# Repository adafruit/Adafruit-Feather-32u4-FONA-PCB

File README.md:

## Adafruit Feather 32u4 FONA PCB
<a href="http://www.adafruit.com/products/3027"><br/>
Click here to purchase one from the Adafruit shop</a>

This is the Adafruit Feather 32u4 FONA - our take on an 'all-in-one' Arduino-compatible + audio/sms/data capable cellular with built in USB and battery charging. Its an Adafruit Feather 32u4 with a FONA800 module, ready to rock! We have other boards and accessories in the Feather family, check'em out here.

At the Feather 32u4's heart is at ATmega32u4 clocked at 8 MHz and at 3.3V logic, a chip setup we've had tons of experience with as it's the same as the Flora. This chip has 32K of flash and 2K of RAM, with built in USB so not only does it have a USB-to-Serial program & debug capability built in with no need for an FTDI-like chip, it can also act like a mouse, keyboard, USB MIDI device, etc.

Since you'll be taking this on the road, we added a connector for any of our 3.7V Lithium polymer batteries and built in battery charging. A 500mAh+ Lipoly battery is required for use, it keeps the cellular module happy during the high current spikes. Plug the Feather into microUSB to charge at 500mA.

PCB files for Adafruit Feather 32u4 FONA. The format is EagleCAD schematic and board layout
- https://www.adafruit.com/product/3027

### License

Adafruit invests time and resources providing this open source design, please support Adafruit and open-source hardware by purchasing products from [Adafruit](https://www.adafruit.com)!

All text above must be included in any redistribution

Designed by Limor Fried/Ladyada for Adafruit Industries.
Creative Commons Attribution/Share-Alike, all text above must be included in any redistribution. 
See license.txt for additional information.

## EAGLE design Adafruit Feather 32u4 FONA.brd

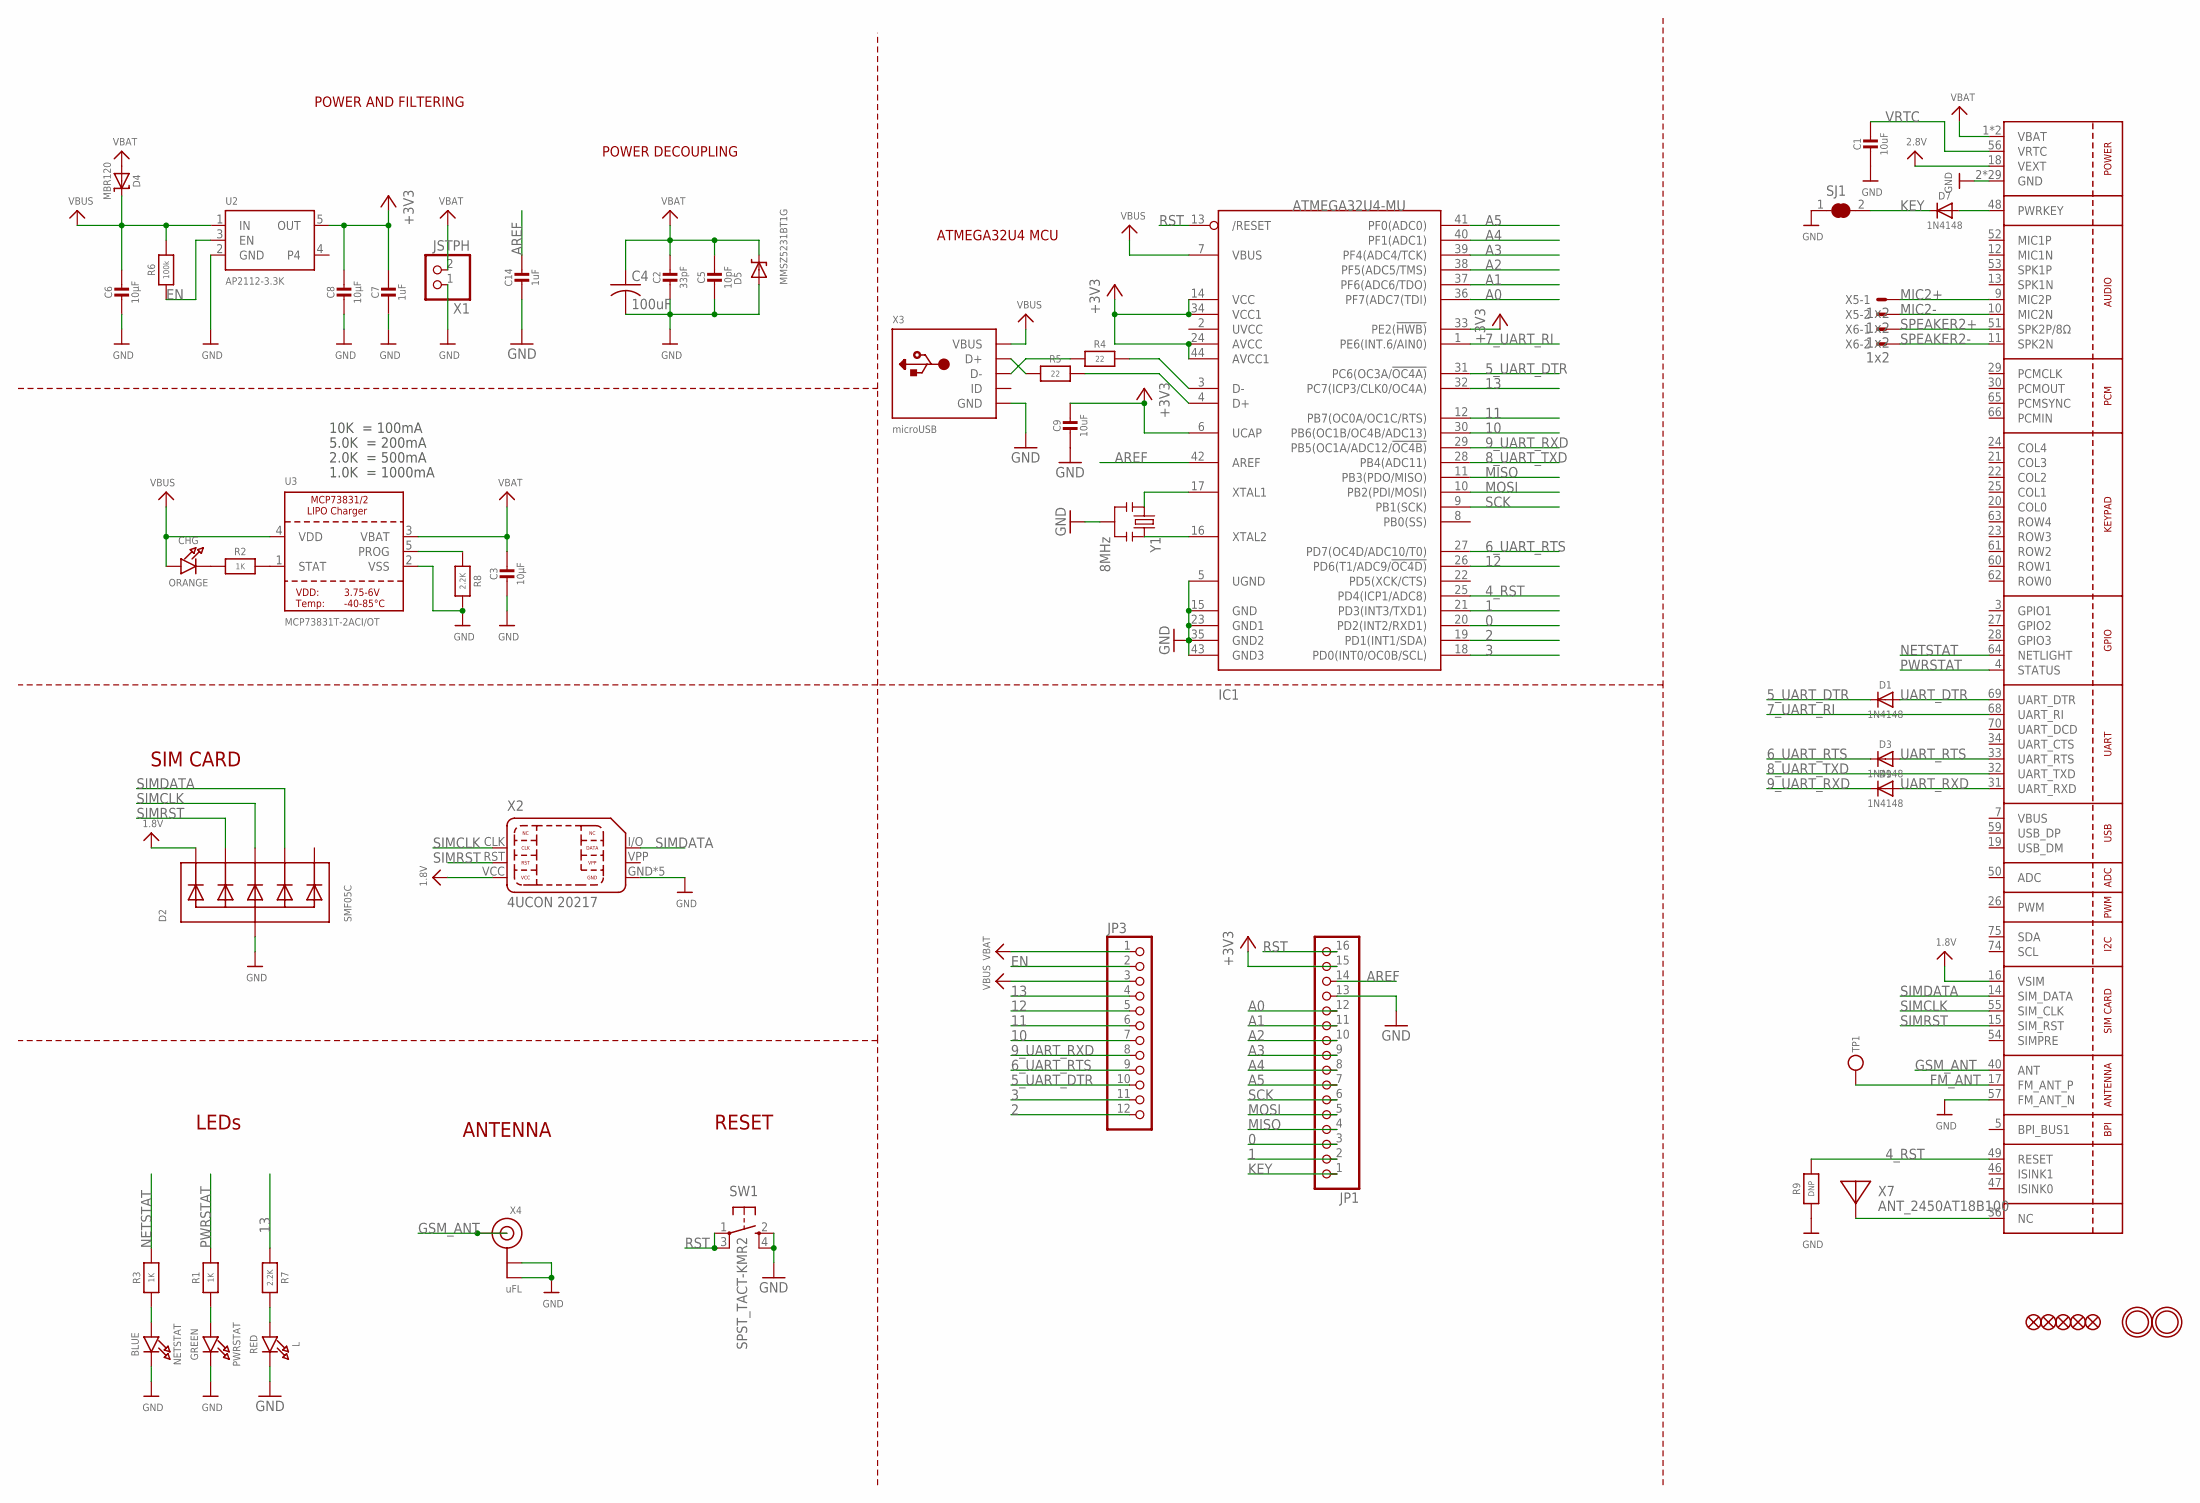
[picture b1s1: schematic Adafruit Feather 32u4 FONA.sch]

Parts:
C1, C9: 10uF; _0805MP
C2: 33pF; 0805-NO
C3, C6, C8: 10µF; 0805-NO
C4: 100uF; C1210
C5: 10pF; 0805-NO
C7, C14: 1uF; 0603-NO
CHG: ORANGE; CHIPLED_0805_NOOUTLINE
D1, D3, D7, D9: 1N4148; SOD-323
D2: SMF05C; SOT363
D4: MBR120; SOD-123
D5: MMSZ5231BT1G; SOD-123
IC1: ATMEGA32U4-MU; TQFN44_7MM
JP1: HEADER-1X16ROUND; 1X16_ROUND
JP3: HEADER-1X12; 1X12_ROUND
L: RED; CHIPLED_0805_NOOUTLINE
NETSTAT: BLUE; CHIPLED_0805_NOOUTLINE
PWRSTAT: GREEN; CHIPLED_0805_NOOUTLINE
R1, R2, R3: 1K; 0603-NO
R4, R5: 22; 0603-NO
R6: 100k; 0603-NO
R7, R8: 2.2K; 0603-NO
R9: DNP; 0603-NO
SJ1: SOLDERJUMPER_CLOSED; SOLDERJUMPER_CLOSEDWIRE
SW1: SPST_TACT-KMR2; KMR2
TP1: TESTPOINTROUND1.5MM; TESTPOINT_ROUND_1.5MM
U1: SIM800H/L; SIM800L
U2: AP2112-3.3K; SOT23-5
U3: MCP73831T-2ACI/OT; SOT23-5
U$18, U$23, U$34, U$35, U$42: FIDUCIAL""; FIDUCIAL_1MM
U$31, U$32: MOUNTINGHOLE2.5; MOUNTINGHOLE_2.5_PLATED
X1: JSTPH; JSTPH2
X2: 4UCON 20217; 4UCONN_20217
X3: microUSB; 4UCONN_20329_V2
X4: uFL; U.FL
X5, X6: 1x2; 87758-0216
X7: ANT_2450AT18B100
Y1: 8MHz; RESONATOR-SMD

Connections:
0: IC1.20 (PD2(INT2/RXD1)), JP1.3
1: IC1.21 (PD3(INT3/TXD1)), JP1.2
1.8V: D2.1 (C1), U1.16 (VSIM), X2.VCC
2: IC1.19 (PD1(INT1/SDA)), JP3.12
2.8V: U1.18 (VEXT)
3: IC1.18 (PD0(INT0/OC0B/SCL)), JP3.11
4_RST: IC1.25 (PD4(ICP1/ADC8)), R9.2, U1.49 (RESET)
5_UART_DTR: D1.C, IC1.31 (PC6(OC3A/!OC4A)), JP3.10
6_UART_RTS: D3.C, IC1.27 (PD7(OC4D/ADC10/T0)), JP3.9
7_UART_RI: IC1.1 (PE6(INT.6/AIN0)), U1.68 (UART_RI)
8_UART_TXD: IC1.28 (PB4(ADC11)), U1.32 (UART_TXD)
9_UART_RXD: D9.C, IC1.29 (PB5(OC1A/ADC12/!OC4B)), JP3.8
10: IC1.30 (PB6(OC1B/OC4B/ADC13)), JP3.7
11: IC1.12 (PB7(OC0A/OC1C/RTS)), JP3.6
12: IC1.26 (PD6(T1/ADC9/!OC4D)), JP3.5
13: IC1.32 (PC7(ICP3/CLK0/OC4A)), JP3.4, R7.1
+3V3: C7.1, C8.1, C9.1, IC1.6 (UCAP), IC1.14 (VCC), IC1.24 (AVCC), IC1.33 (PE2(!HWB)), IC1.34 (VCC1), IC1.44 (AVCC1), JP1.15, U2.5 (OUT)
A0: IC1.36 (PF7(ADC7(TDI)), JP1.12
A1: IC1.37 (PF6(ADC6/TDO)), JP1.11
A2: IC1.38 (PF5(ADC5/TMS)), JP1.10
A3: IC1.39 (PF4(ADC4/TCK)), JP1.9
A4: IC1.40 (PF1(ADC1)), JP1.8
A5: IC1.41 (PF0(ADC0)), JP1.7
AREF: C14.1, IC1.42 (AREF), JP1.14
D+: IC1.4 (D+), R5.2
D-: IC1.3 (D-), R4.2
EN: JP3.2, R6.1, U2.3 (EN)
FM_ANT: TP1.P$1, U1.17 (FM_ANT_P)
GND: C1.2, C2.2, C3.2, C4.2, C5.2, C6.2, C7.2, C8.2, C9.2, C14.2, D2.2 (A), D5.A, IC1.5 (UGND), IC1.15 (GND), IC1.23 (GND1), IC1.35 (GND2), IC1.43 (GND3), JP1.13, L.C, NETSTAT.C, PWRSTAT.C, R8.2, R9.1, SJ1.1, SW1.2 (S), SW1.4 (S1), U1.2 (GND), U1.6 (GND), U1.8 (GND), U1.35 (GND), U1.37 (GND), U1.38 (GND), U1.39 (GND), U1.41 (GND), U1.43 (GND), U1.44 (GND), U1.45 (GND), U1.57 (FM_ANT_N), U1.58 (GND), U1.67 (GND), U1.71 (GND), U1.72 (GND), U1.73 (GND), U1.76 (GND), U1.77 (GND), U1.78 (GND), U1.79 (GND), U1.80 (GND), U1.81 (GND), U1.82 (GND), U1.83 (GND), U1.84 (GND), U1.85 (GND), U1.86 (GND), U1.87 (GND), U1.88 (GND), U2.2 (GND), U3.2 (VSS), X1.1, X2.GND, X2.GND@1 (GND), X2.GND@2 (GND), X2.GND@3 (GND), X2.GND@4 (GND), X3.BASE@1 (GND), X3.BASE@2 (GND), X3.GND, X3.SPRT@1 (GND), X3.SPRT@2 (GND), X3.SPRT@3 (GND), X3.SPRT@4 (GND), X4.1 (GND), X4.2 (GND), Y1.2
GSM_ANT: U1.40 (ANT), X4.3 (SIGNAL)
KEY: D7.C, JP1.1, SJ1.2
MIC2+: U1.9 (MIC2P), X5.1
MIC2-: U1.10 (MIC2N), X5.2
MISO: IC1.11 (PB3(PDO/MISO)), JP1.4
MOSI: IC1.10 (PB2(PDI/MOSI)), JP1.5
unnamed: CHG.C, R2.1
unnamed: L.A, R7.2
unnamed: R2.2, U3.1 (STAT)
unnamed: R8.1, U3.5 (PROG)
unnamed: PWRSTAT.A, R1.1
unnamed: U1.36 (NC), X7.FP
unnamed: D7.A, U1.48 (PWRKEY)
unnamed: NETSTAT.A, R3.1
unnamed: IC1.16 (XTAL2), Y1.3
unnamed: IC1.17 (XTAL1), Y1.1
unnamed: R5.1, X3.D+
unnamed: R4.1, X3.D-
NETSTAT: R3.2, U1.64 (NETLIGHT)
PWRSTAT: R1.2, U1.4 (STATUS)
RST: IC1.13 (/RESET), JP1.16, SW1.1, SW1.3 (P1)
SCK: IC1.9 (PB1(SCK)), JP1.6
SIMCLK: D2.4 (C3), U1.55 (SIM_CLK), X2.CLK
SIMDATA: D2.5 (C4), U1.14 (SIM_DATA), X2.I/O (DATA)
SIMRST: D2.3 (C2), U1.15 (SIM_RST), X2.RST
SPEAKER2+: U1.51 (SPK2P/8Ω), X6.1
SPEAKER2-: U1.11 (SPK2N), X6.2
UART_DTR: D1.A, U1.69 (UART_DTR)
UART_RTS: D3.A, U1.33 (UART_RTS)
UART_RXD: D9.A, U1.31 (UART_RXD)
VBAT: C2.1, C3.1, C4.1, C5.1, D4.A, D5.C, JP3.1, U1.1 (VBAT), U1.42 (VBAT), U3.3 (VBAT), X1.2
VBUS: C6.1, CHG.A, D4.C, IC1.7 (VBUS), JP3.3, R6.2, U1.7 (VBUS), U2.1 (IN), U3.4 (VDD), X3.VBUS
VRTC: C1.1, U1.56 (VRTC)

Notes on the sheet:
POWER AND FILTERING
RESET
ATMEGA32U4 MCU
10K = 100mA
5.0K = 200mA
2.0K = 500mA
1.0K = 1000mA
ANTENNA
SIM CARD
POWER DECOUPLING
LEDs

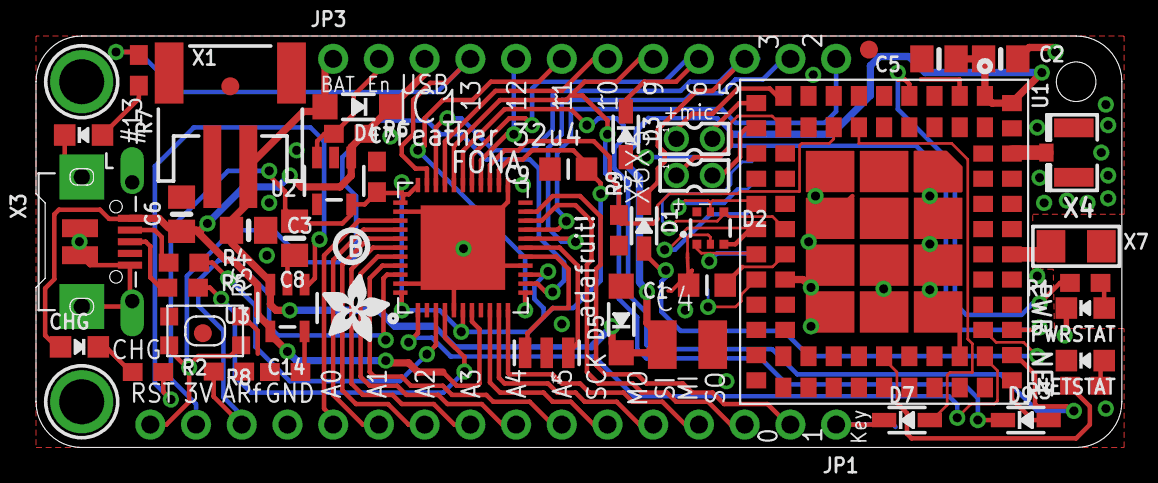
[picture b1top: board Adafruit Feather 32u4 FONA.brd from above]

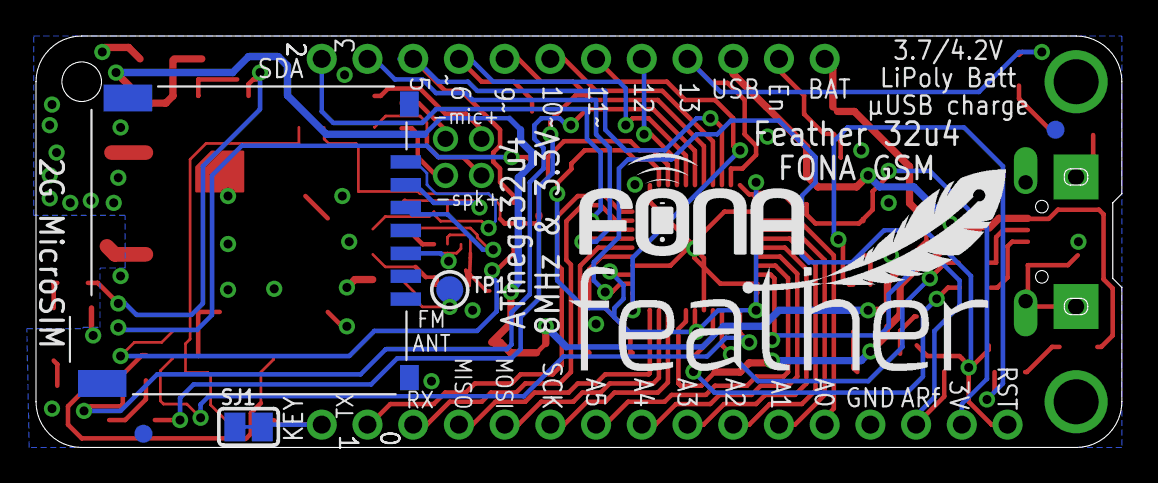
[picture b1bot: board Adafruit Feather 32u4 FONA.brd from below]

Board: 2 copper layers, 60.3 x 22.9 mm, 58 parts (7 on the bottom side), 61 nets.

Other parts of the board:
U$7: ADAFRUIT_3.5MM
U$25: FEATHERLOGO
U$43: FONA_LOGO_SMALL
U$44: PCBFEAT-REV-040

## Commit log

2016-04-27 PCB files!

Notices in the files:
parts and their libraries:
microbuilder: This work is placed in the public domain, and may be freely used for commercial and non-commercial work with the following conditions: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
SparkFun: Licensing: CC v3.0 Share-Alike You are welcome to use this library for commercial purposes.
